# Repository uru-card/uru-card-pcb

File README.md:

# URU Card PCB

[URU Card](https://github.com/uru-card/uru-card) is an Arduino based FIDO2 Authenticator. This repository contains Eagle CAD design files to build the device.

## Schematic

The schematic for the URU Card is presented on the figure below:

Components requried to build the device

* ESP32 Pico D4 microcontroller
* ATECC508A or ATECC608A
* MPR121 touch keyboard controller
* SSD1306 based OLED display
* AP2112 voltage regulator
* MicroUSB socket
* A bunch of 0603 resistors and capacitors

## Mainboard PCB

The components are mounted on the mainboard. In fact it's the only PCB required to build the device.

## Authors

* [**Andrey Ovcharov**](https://github.com/snakeye) - project owner

See also the list of [contributors](https://github.com/uru-card/uru-card/contributors) who participated in this project.

## References

* [Information about URU Card project](https://en.ovcharov.me/category/fido2/)

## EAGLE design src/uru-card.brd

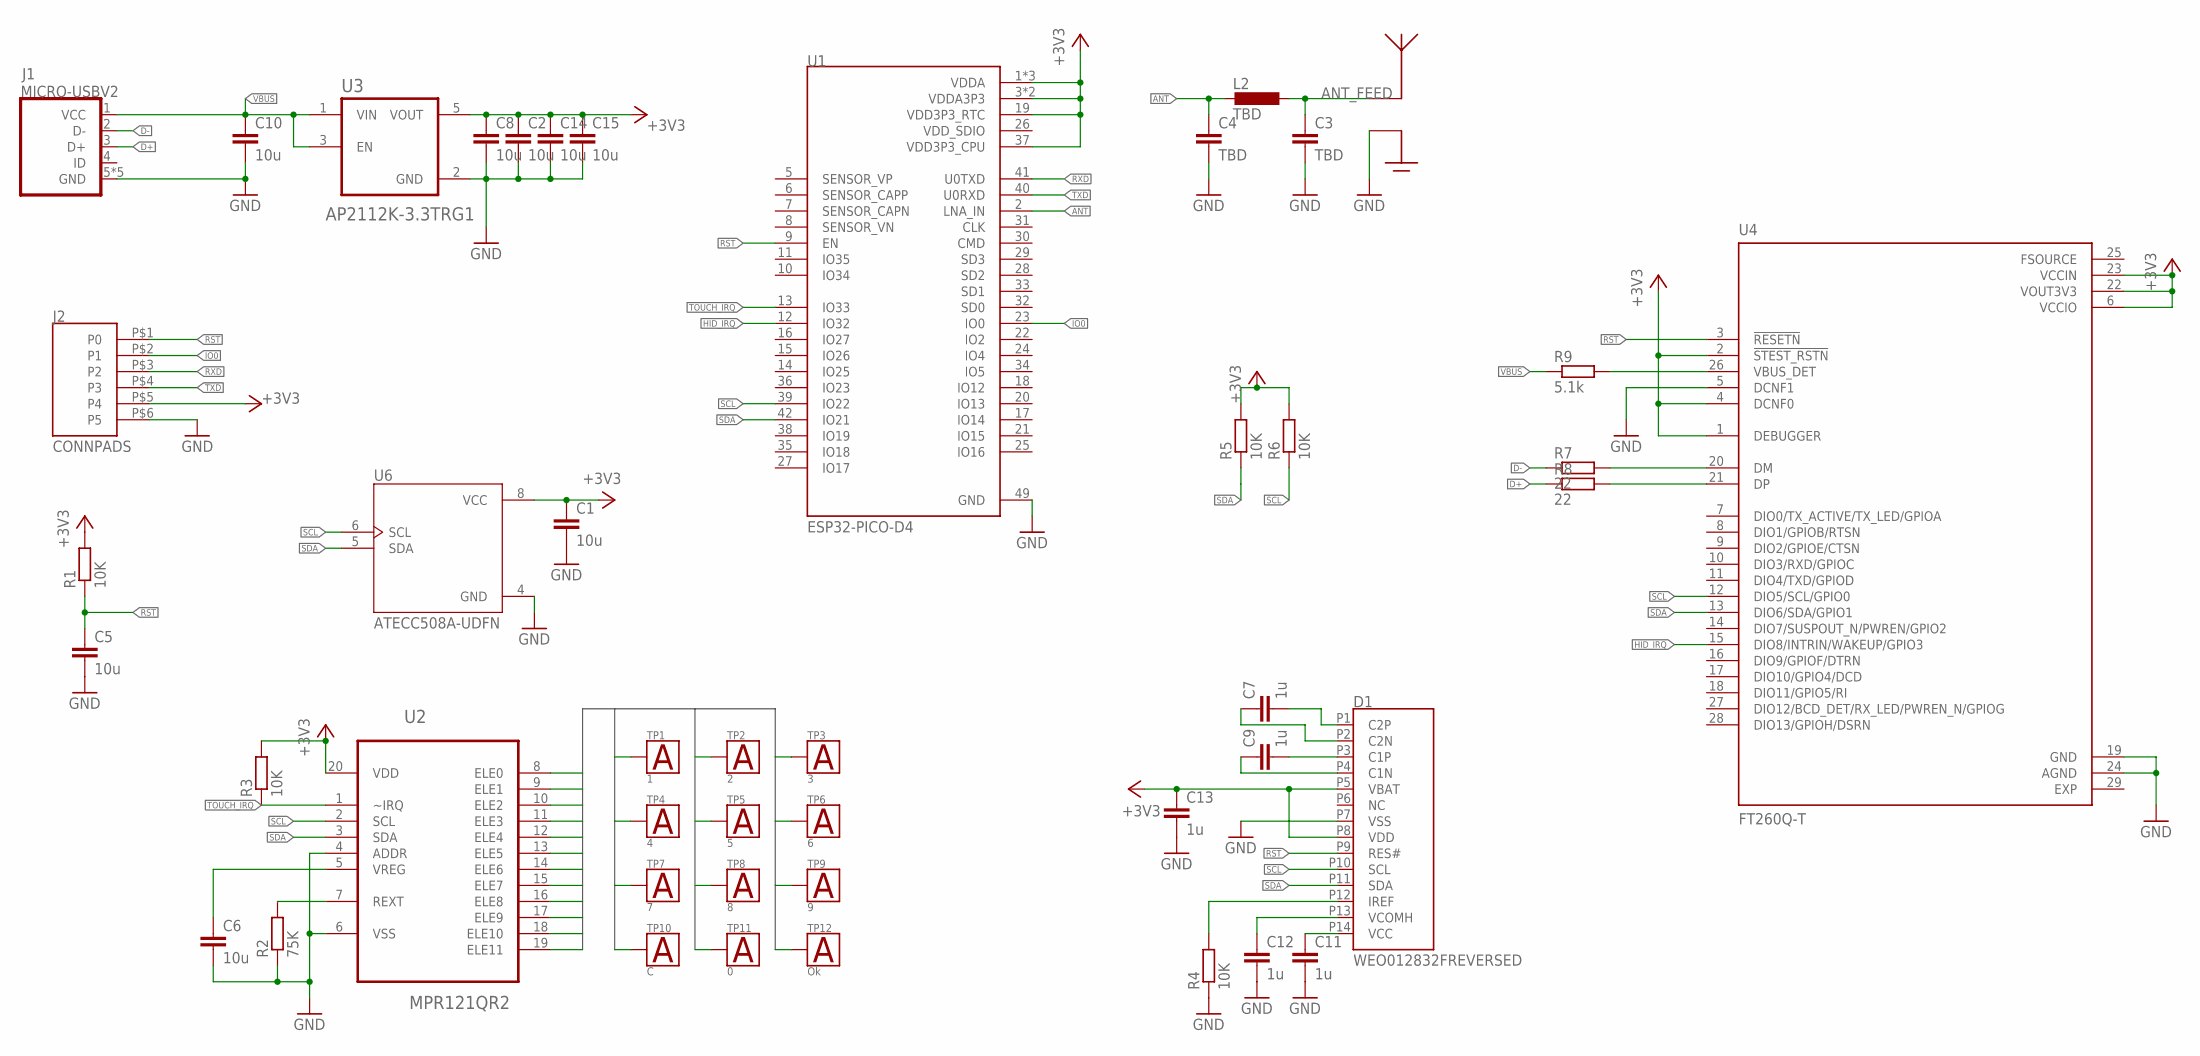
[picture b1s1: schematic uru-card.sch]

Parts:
C1, C2, C5, C6, C8, C10, C14, C15: 10u; C0603
C3, C4: TBD; C0603
C7, C9, C11, C12, C13: 1u; C0603
D1: WEO012832FREVERSED; WEO012832F-REVERSE
J1: MICRO-USBV2; MICRO-USB-2
J2: CONNPADS; PADS
L2: TBD; L2012C
R1, R3, R4, R5, R6: 10K; R0603
R2: 75K; R0603
R7, R8: 22; R0603
R9: 5.1k; R0603
TP1: 1; TOUCH
TP2: 2; TOUCH
TP3: 3; TOUCH
TP4: 4; TOUCH
TP5: 5; TOUCH
TP6: 6; TOUCH
TP7: 7; TOUCH
TP8: 8; TOUCH
TP9: 9; TOUCH
TP10: C; TOUCH
TP11: 0; TOUCH
TP12: Ok; TOUCH
U1: ESP32-PICO-D4; PQFN50P700X700X104-49N
U2: MPR121QR2; QFN40P300X300X60-20N
U3: AP2112K-3.3TRG1; SOT95P285X140-5N
U4: FT260Q-T; QFN50P500X500X80-29N
U6: ATECC508A-UDFN; SON50P200X300X60-9N
U$15: ANT-2_4_PCB; ANT-2_4

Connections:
0: TP11.P$1, U2.18 (ELE10)
1: TP1.P$1, U2.8 (ELE0)
2: TP2.P$1, U2.9 (ELE1)
3: TP3.P$1, U2.10 (ELE2)
4: TP4.P$1, U2.11 (ELE3)
5: TP5.P$1, U2.12 (ELE4)
6: TP6.P$1, U2.13 (ELE5)
7: TP7.P$1, U2.14 (ELE6)
8: TP8.P$1, U2.15 (ELE7)
9: TP9.P$1, U2.16 (ELE8)
+3V3: C1.1, C2.1, C8.1, C13.1, C14.1, C15.1, D1.P5 (VBAT), D1.P8 (VDD), J2.P$5 (P4), R1.2, R3.2, R5.2, R6.2, U1.1 (VDDA), U1.3 (VDDA3P3), U1.4 (VDDA3P3), U1.19 (VDD3P3_RTC), U1.37 (VDD3P3_CPU), U1.43 (VDDA), U1.46 (VDDA), U2.20 (VDD), U3.5 (VOUT), U4.1 (DEBUGGER), U4.2 (!STEST_RSTN), U4.4 (DCNF0), U4.6 (VCCIO), U4.22 (VOUT3V3), U4.23 (VCCIN), U6.8 (VCC)
ANT: C4.1, L2.2, U1.2 (LNA_IN)
ANT_FEED: C3.1, L2.1, U$15.FEED
C: TP10.P$1, U2.17 (ELE9)
D+: J1.3 (D+), R8.1
D-: J1.2 (D-), R7.1
EXP: U4.29 (EXP)
FSOURCE: U4.25 (FSOURCE)
GND: C1.2, C2.2, C3.2, C4.2, C5.2, C6.2, C8.2, C10.2, C11.2, C12.2, C13.2, C14.2, C15.2, D1.P7 (VSS), J1.5 (GND), J1.P$1 (GND), J1.P$2 (GND), J1.P$3 (GND), J1.P$4 (GND), J2.P$6 (P5), R2.1, R4.1, U1.49 (GND), U2.4 (ADDR), U2.6 (VSS), U3.2 (GND), U4.5 (DCNF1), U4.19 (GND), U4.24 (AGND), U6.4 (GND), U$15.GND
HID_IRQ: U1.12 (IO32), U4.15 (DIO8/INTRIN/WAKEUP/GPIO3)
IO0: J2.P$2 (P1), U1.23 (IO0)
unnamed: C9.1, D1.P4 (C1N)
unnamed: C9.2, D1.P3 (C1P)
unnamed: C7.1, D1.P2 (C2N)
unnamed: C7.2, D1.P1 (C2P)
unnamed: R7.2, U4.20 (DM)
unnamed: D1.P12 (IREF), R4.2
unnamed: C12.1, D1.P13 (VCOMH)
unnamed: C11.1, D1.P14 (VCC)
unnamed: R8.2, U4.21 (DP)
unnamed: R9.2, U4.26 (VBUS_DET)
unnamed: R2.2, U2.7 (REXT)
unnamed: C6.1, U2.5 (VREG)
OK: TP12.P$1, U2.19 (ELE11)
RST: C5.1, D1.P9 (RES#), J2.P$1 (P0), R1.1, U1.9 (EN), U4.3 (!RESETN)
RXD: J2.P$3 (P2), U1.41 (U0TXD)
SCL: D1.P10 (SCL), R6.1, U1.39 (IO22), U2.2 (SCL), U4.12 (DIO5/SCL/GPIO0), U6.6 (SCL)
SDA: D1.P11 (SDA), R5.1, U1.42 (IO21), U2.3 (SDA), U4.13 (DIO6/SDA/GPIO1), U6.5 (SDA)
TOUCH_IRQ: R3.1, U1.13 (IO33), U2.1 (~IRQ)
TXD: J2.P$4 (P3), U1.40 (U0RXD)
VBUS: C10.1, J1.1 (VCC), R9.1, U3.1 (VIN), U3.3 (EN)
VDD_SDIO: U1.26 (VDD_SDIO)

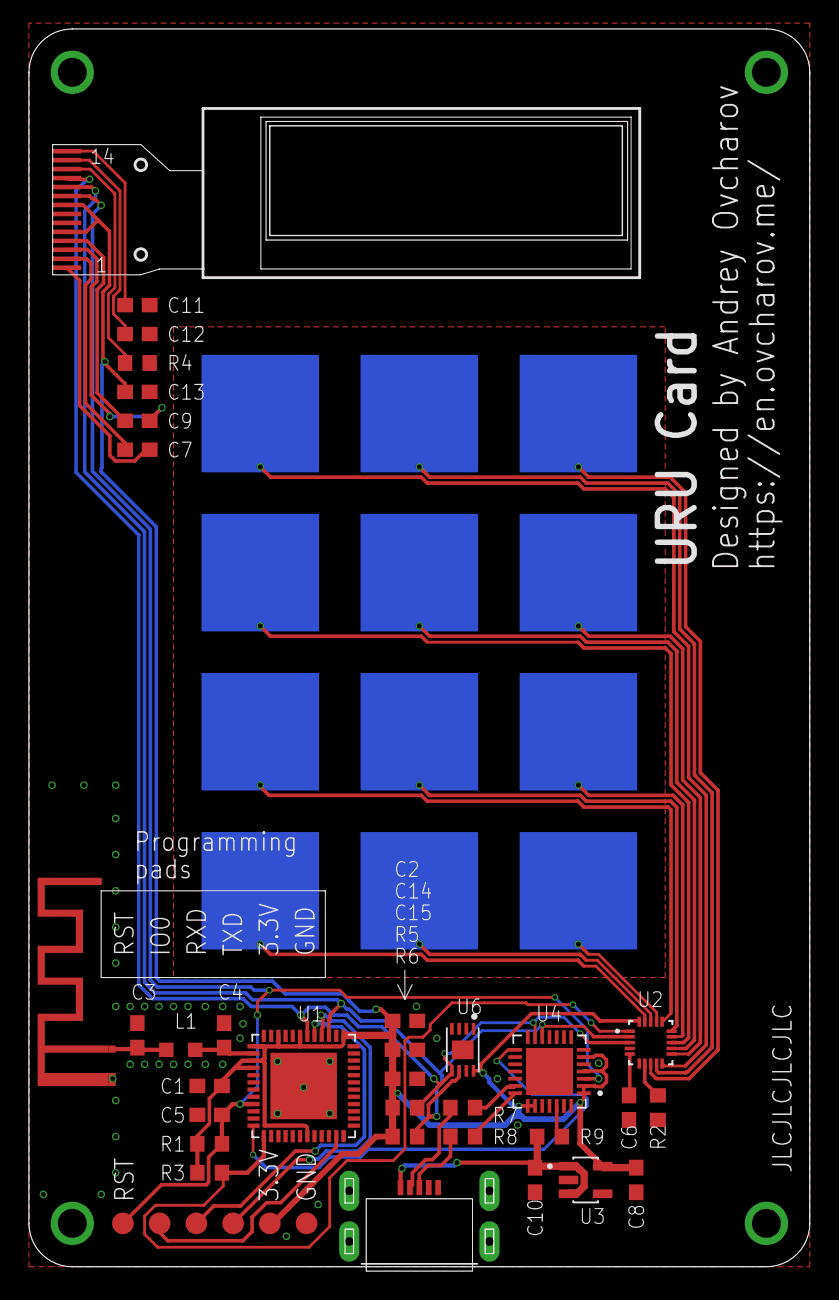
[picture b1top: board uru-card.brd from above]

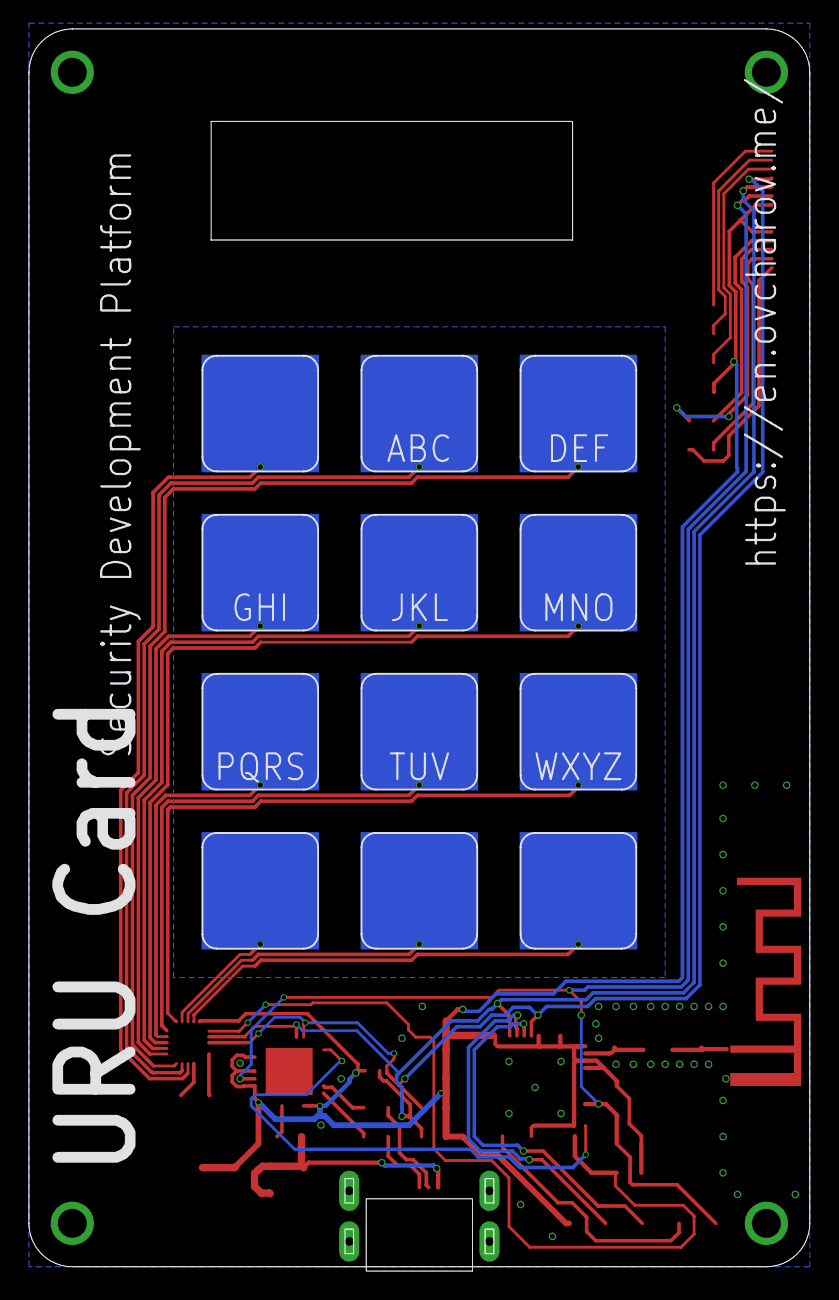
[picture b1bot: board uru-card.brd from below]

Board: 2 copper layers, 54.0 x 85.9 mm, 46 parts (12 on the bottom side), 39 nets.

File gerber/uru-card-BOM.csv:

Comment,Designator,Footprint,LCSC Part #,Qty,Value,Device,Package,Parts,Description,AVAILABILITY,DESCRIPTION,MF,MP,PACKAGE,POPULARITY,PRICE,SPICEPREFIX
10K,"R1, R3, R4, R5, R6",R0603,C25804,5,,R-EU_R0603,,,"RESISTOR, European symbol",,,,,,70,,R
10u,"C1, C2, C5, C6, C8, C10, C14, C15",C0603,C19702,8,,C-EUC0603,,,"CAPACITOR, European symbol",,,,,,73,,C
1u,"C7, C9, C11, C12, C13",C0603,C15849,5,,C-EUC0603,,,"CAPACITOR, European symbol",,,,,,73,,C
75K,R2,R0603,C23242,1,,R-EU_R0603,,,"RESISTOR, European symbol",,,,,,70,,R
AP2112K-3.3TRG1,U3,SOT95P285X140-5N,C51118 ,1,,AP2112K-3.3TRG1,,,AP2112 Series 0.6 A 3.3 V Fixed Output SMT LDO Linear Regulator - SOT23-5,Unavailable, AP2112 Series 0.6 A 3.3 V Fixed Output SMT LDO Linear Regulator - SOT23-5 ,Diodes Inc.,AP2112K-3.3TRG1,SOT-753 Diodes Inc.,,None,
ATECC508A-UDFN,U6,SON50P200X300X60-9N,C145574,1,,ATECC508A-UDFN,,,,,,,,,,,
ESP32-PICO-D4,U1,PQFN50P700X700X104-49N,C193707 ,1,,ESP32-PICO-D4,,,"The ESP32-PICO-D4 is a System-in-Package (SIP) module that is based on ESP32, providing complete Wi-Fi",Unavailable, WIFi/Bluetooth SIP ,Espressif Systems,ESP32-PICO-D4,SMD-48 Espressif Systems,,None,
MICRO-USBV2,J1,MICRO-USB-2,C40958,1,,MICRO-USBV2,,,Micro USB B connector,,,,,,,,
MPR121QR2,U2,QFN40P300X300X60-20N,C91322,1,,MPR121QR2,,,Proximity Capacitive Touch Sensor Controller,Unavailable," Capacitive Touch Buttons, Slider, Wheel 20-QFN _3x3_ ",NXP USA,MPR121QR2,QFN-20 Resurgent,,None,
TBD,L2,L2012C,C21189,1,,L-EUL2012C,,,"INDUCTOR, European symbol",,,,,,2,,L

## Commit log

2020-04-16 Added FT260Q USB I2C
2020-04-16 Routed USB HID
2020-04-16 Changed routing for the display component
2020-08-31 Design refactoring
    Replaced the antenna with PCB one
    Moved connector
    Replaced tantalum capacitor with ceramic ones
2020-09-01 v1.1
2020-09-02 fixed the trace crossing cut out
2020-09-27 Fixed incorrect connections
2020-09-27 Added boards for covering
2020-09-27 Removed wire stub
2020-09-28 Release 1.2
2020-11-10 tiny connector board
2020-11-12 Updated CAM job
2020-11-14 Added part names on the board
2020-11-26 JLCPCB production files
2020-12-03 Improved layout of connector board
